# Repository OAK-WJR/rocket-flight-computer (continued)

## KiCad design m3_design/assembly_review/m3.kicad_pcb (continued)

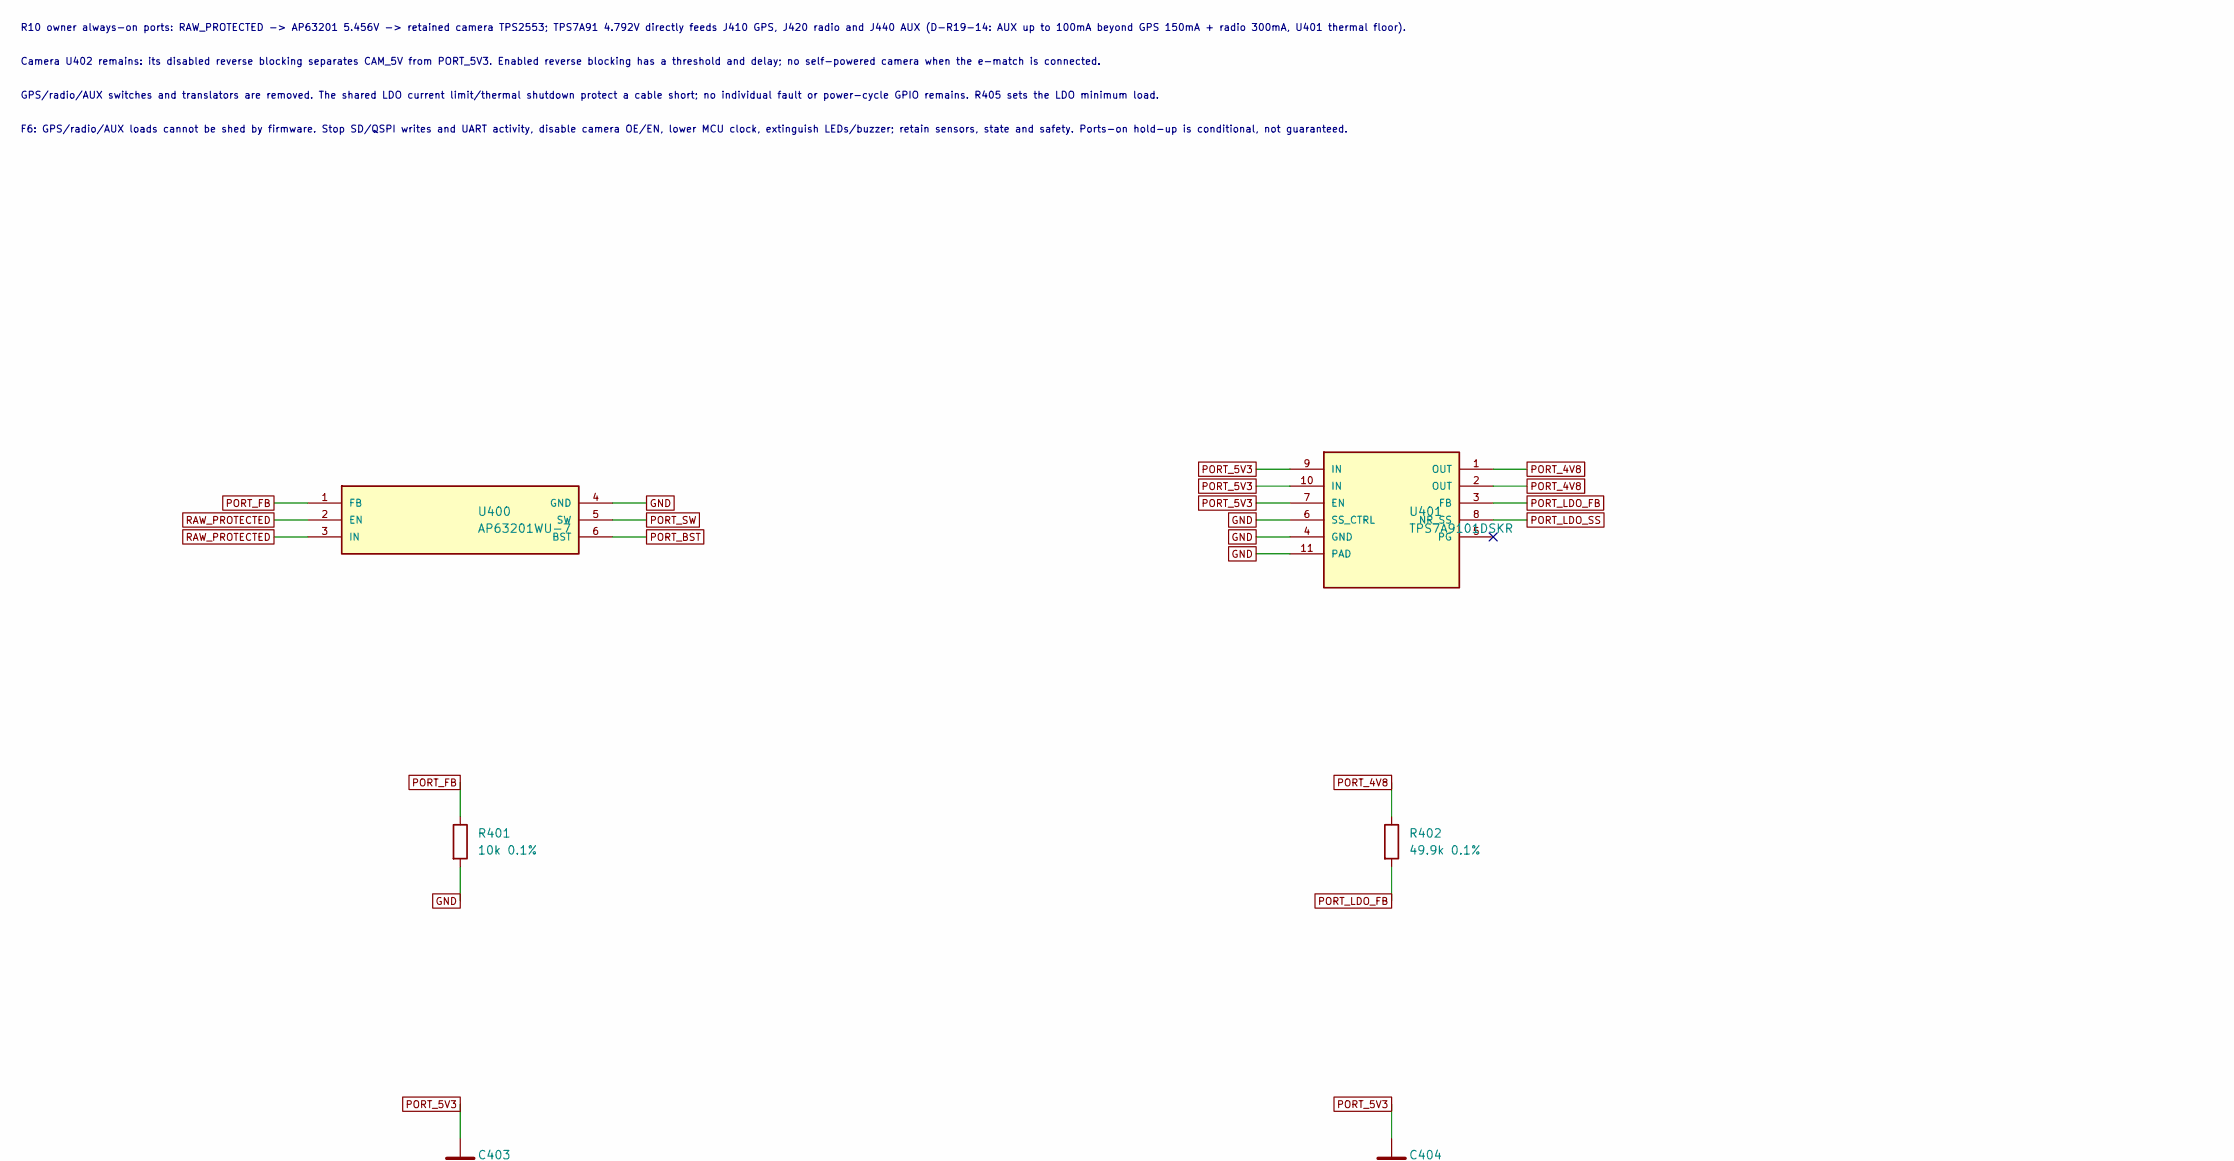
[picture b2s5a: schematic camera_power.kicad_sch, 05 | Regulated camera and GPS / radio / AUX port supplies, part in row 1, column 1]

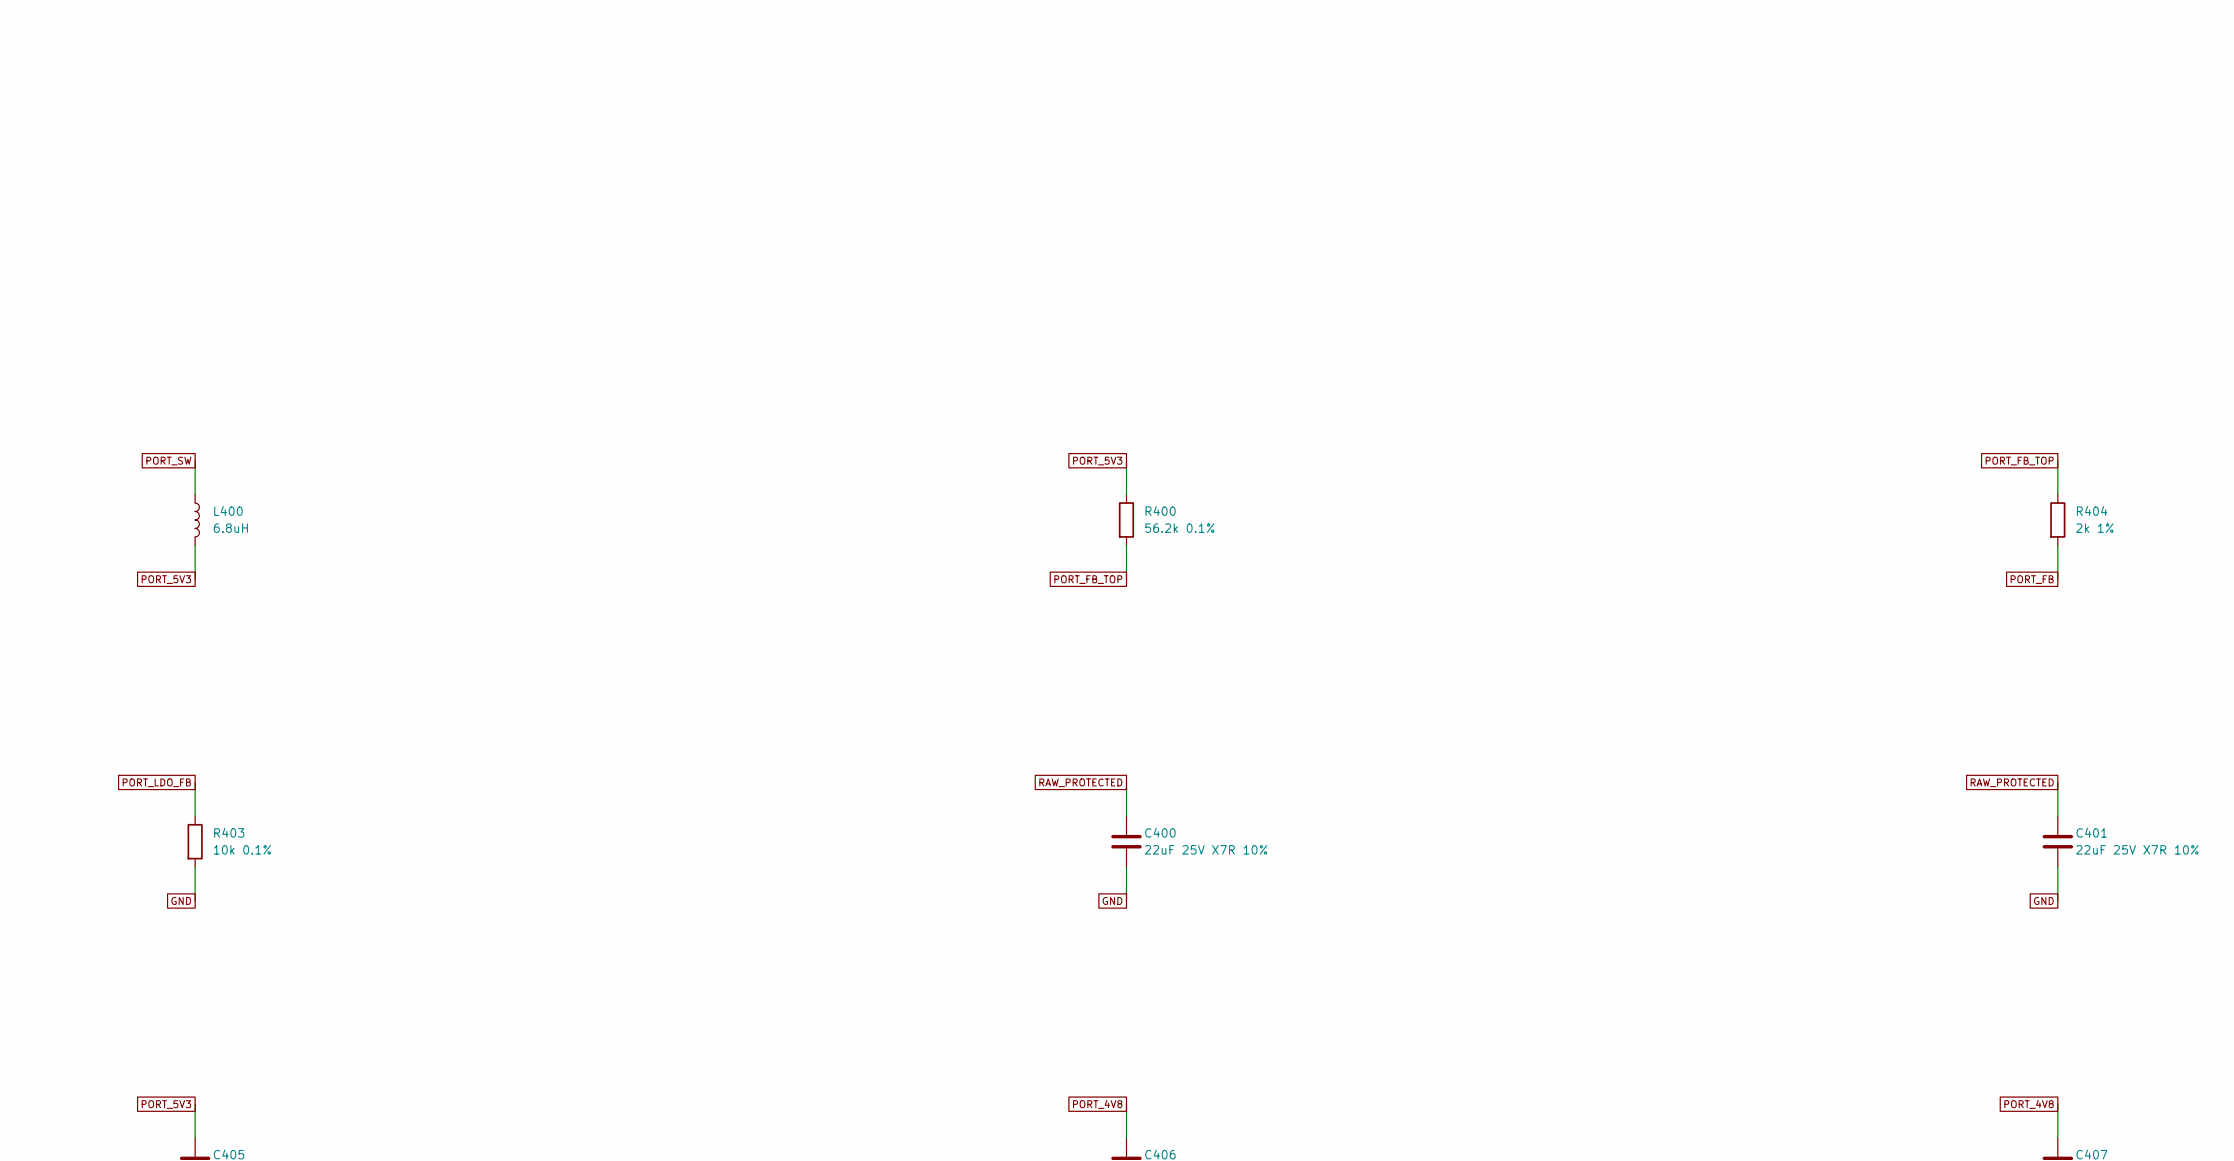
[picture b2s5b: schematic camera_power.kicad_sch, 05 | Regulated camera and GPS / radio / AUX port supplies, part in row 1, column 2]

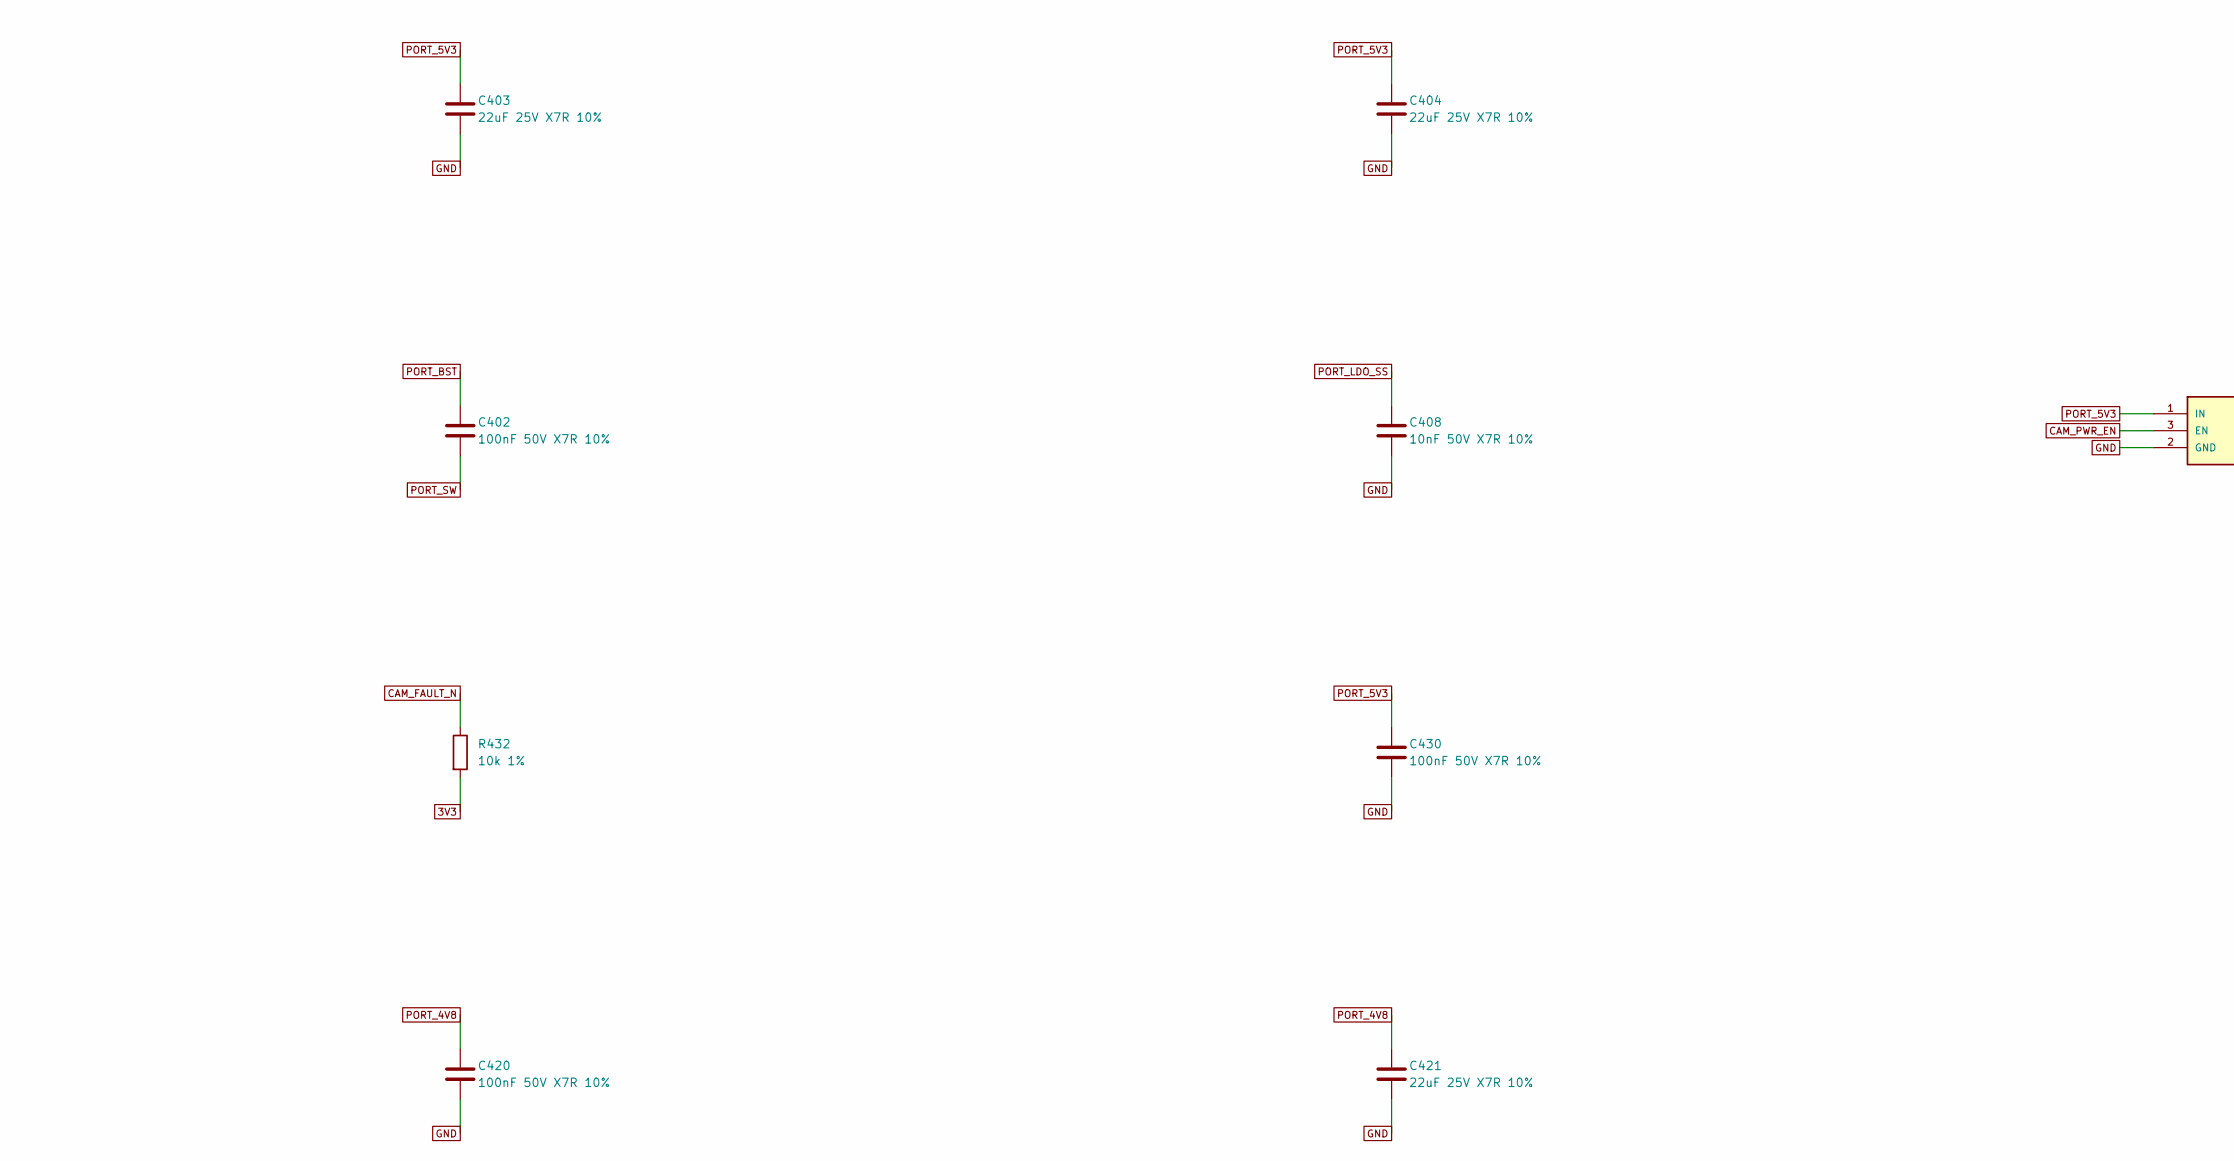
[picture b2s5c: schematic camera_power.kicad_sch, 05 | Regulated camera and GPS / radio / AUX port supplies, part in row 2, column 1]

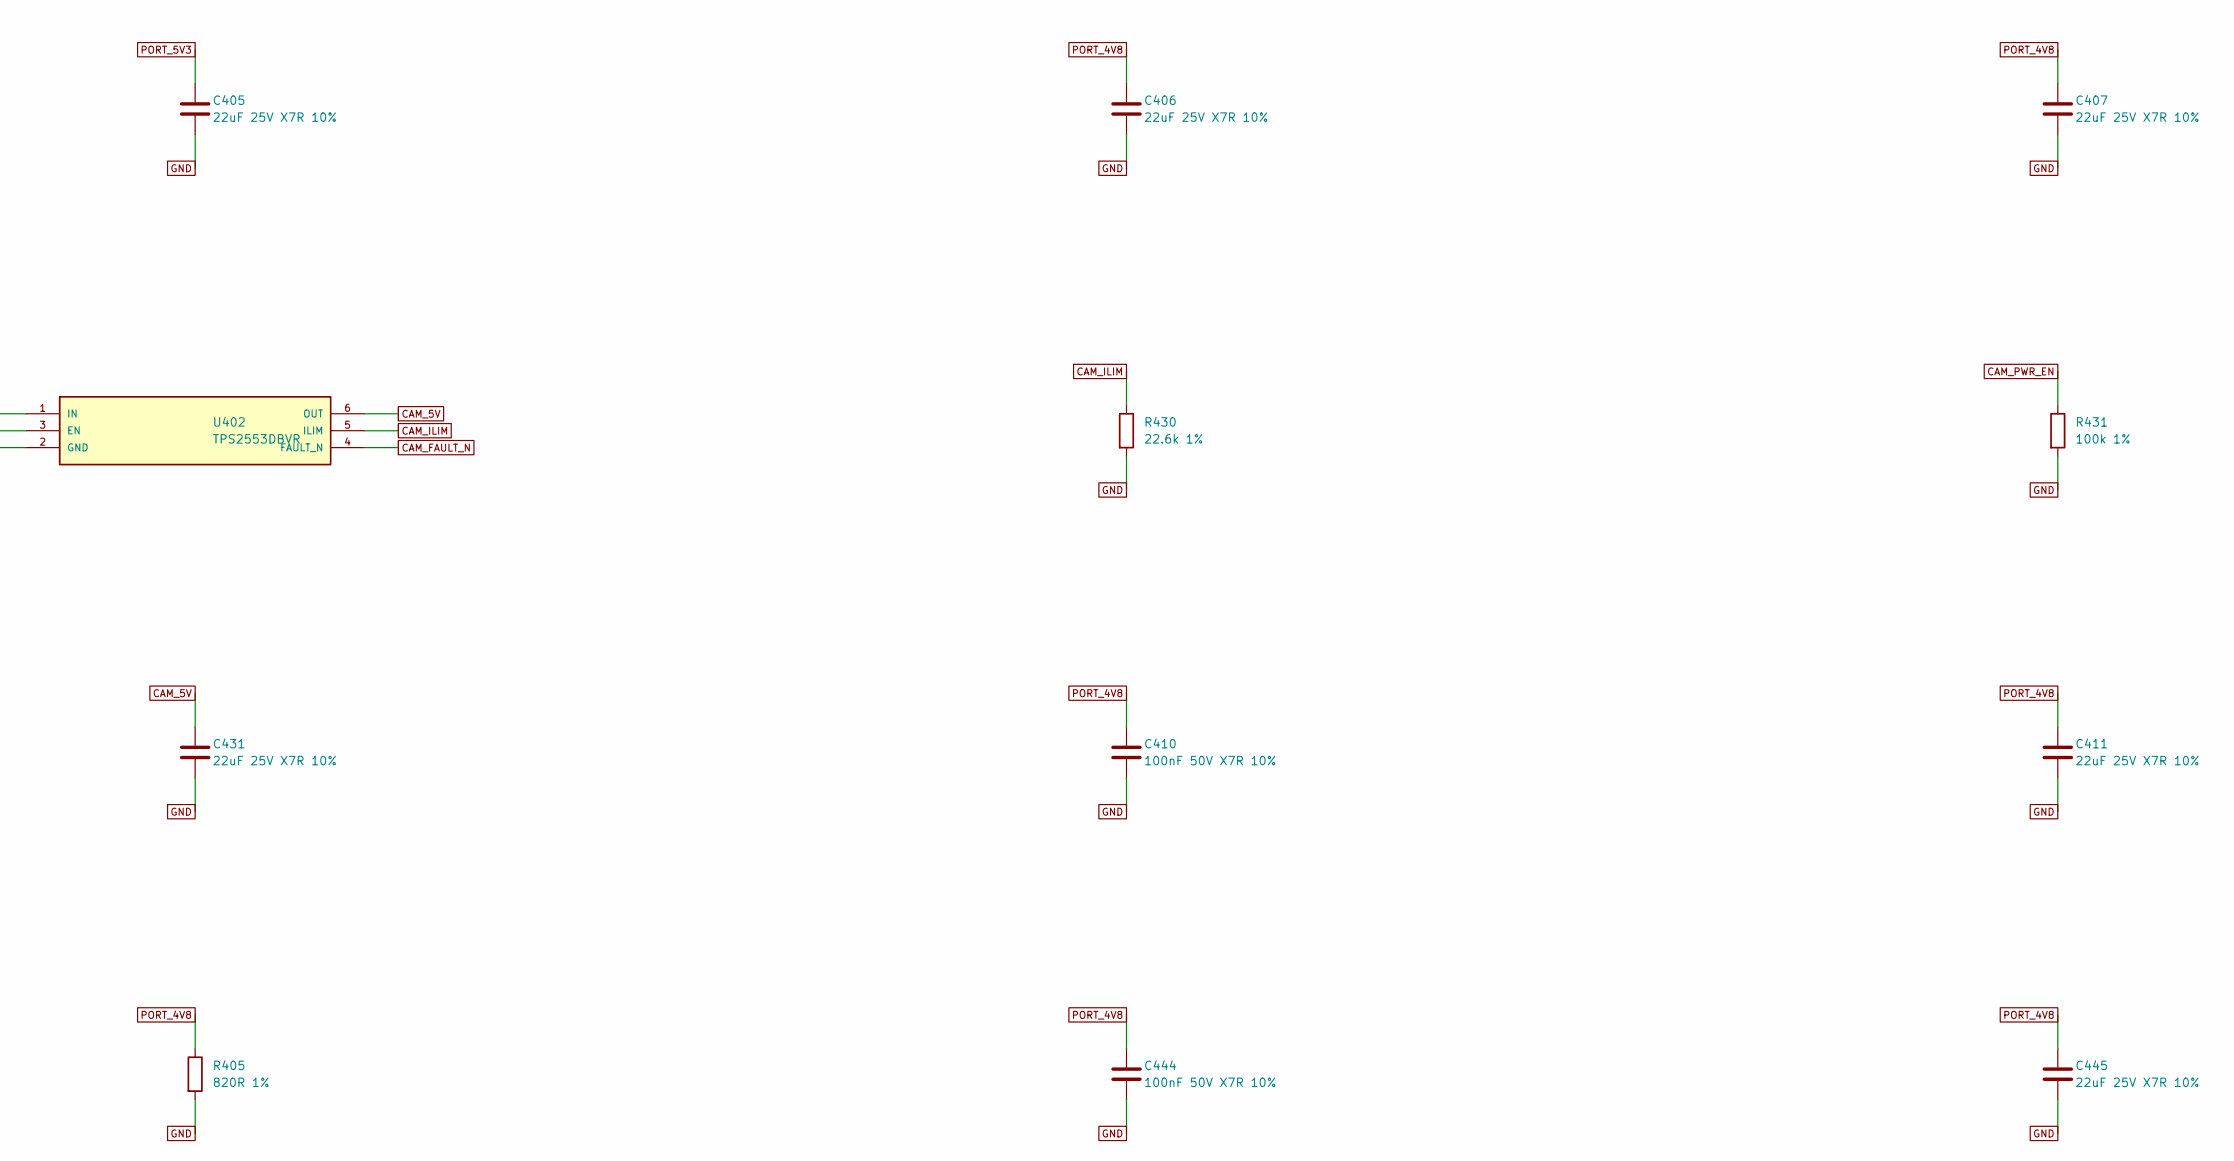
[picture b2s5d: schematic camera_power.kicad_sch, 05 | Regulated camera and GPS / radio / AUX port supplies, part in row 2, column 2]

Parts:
C400, C401, C403, C404, C405, C406, C407, C411, C421, C431, C445: 22uF 25V X7R 10%; M3_GRM32_1210; Manufacturer Part GRM32ER71E226KE15L; LCSC C21397
C402, C410, C420, C430, C444: 100nF 50V X7R 10%; C_0603_1608Metric; Manufacturer Part CC0603KRX7R9BB104; LCSC C14663
C408: 10nF 50V X7R 10%; C0402; Manufacturer Part CL05B103KB5NNNC; LCSC C15195
L400: 6.8uH; M3_SRP5030TA; Manufacturer Part SRP5030T-6R8M; LCSC C1329837
R400: 56.2k 0.1%; R_0603_1608Metric; Manufacturer Part RT0603BRD0756K2L; LCSC C705784
R401, R403: 10k 0.1%; R_0603_1608Metric; Manufacturer Part RT0603BRD0710KL; LCSC C95204
R402: 49.9k 0.1%; R_0603_1608Metric; Manufacturer Part RT0603BRD0749K9L; LCSC C705780
R404: 2k 1%; R_0603_1608Metric; Manufacturer Part 0603WAF2001T5E; LCSC C22975
R405: 820R 1%; R_0603_1608Metric; Manufacturer Part 0603WAF8200T5E; LCSC C23253
R430: 22.6k 1%; R_0603_1608Metric; Manufacturer Part FRC0603F2262TS; LCSC C2999509
R431: 100k 1%; R_0603_1608Metric; Manufacturer Part RC0603FR-07100KL; LCSC C14675
R432: 10k 1%; R0402; Manufacturer Part 0402WGF1002TCE; LCSC C25744
U400: AP63201WU-7; M3_AP63200_TSOT26; Manufacturer Part AP63201WU-7; LCSC C2071044
U401: TPS7A9101DSKR; M3_TPS7A91_DSK10; Manufacturer Part TPS7A9101DSKR; LCSC C2878140
U402: TPS2553DBVR; M3_TPS2553_DBV; Manufacturer Part TPS2553DBVR; LCSC C55266

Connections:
3V3: R432.2; also elsewhere on the board
CAM_5V: C431.1, U402.6 (OUT); also elsewhere on the board
CAM_FAULT_N: R432.1, U402.4 (FAULT_N); also elsewhere on the board
CAM_ILIM: R430.1, U402.5 (ILIM)
CAM_PWR_EN: R431.1, U402.3 (EN); also elsewhere on the board
GND: C400.2, C401.2, C403.2, C404.2, C405.2, C406.2, C407.2, C408.2, C410.2, C411.2, C420.2, C421.2, C430.2, C431.2, C444.2, C445.2, R401.2, R403.2, R405.2, R430.2, R431.2, U400.4 (GND), U401.4 (GND), U401.6 (SS_CTRL), U401.11 (PAD), U402.2 (GND); also elsewhere on the board
PORT_4V8: C406.1, C407.1, C410.1, C411.1, C420.1, C421.1, C444.1, C445.1, R402.1, R405.1, U401.1 (OUT), U401.2 (OUT); also elsewhere on the board
PORT_5V3: C403.1, C404.1, C405.1, C430.1, L400.2, R400.1, U401.7 (EN), U401.9 (IN), U401.10 (IN), U402.1 (IN)
PORT_BST: C402.1, U400.6 (BST)
PORT_FB: R401.1, R404.2, U400.1 (FB)
PORT_FB_TOP: R400.2, R404.1
PORT_LDO_FB: R402.2, R403.1, U401.3 (FB)
PORT_LDO_SS: C408.1, U401.8 (NR_SS)
PORT_SW: C402.2, L400.1, U400.5 (SW)
RAW_PROTECTED: C400.1, C401.1, U400.2 (EN), U400.3 (IN); also elsewhere on the board

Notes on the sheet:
R10 owner always-on ports: RAW_PROTECTED -> AP63201 5.456V -> retained camera TPS2553; TPS7A91 4.792V directly feeds J410 GPS, J420 radio and J440 AUX (D-R19-14: AUX up to 100mA beyond GPS 150mA + radio 300mA, U401 thermal floor).
Camera U402 remains: its disabled reverse blocking separates CAM_5V from PORT_5V3. Enabled reverse blocking has a threshold and delay; no self-powered camera when the e-match is connected.
GPS/radio/AUX switches and translators are removed. The shared LDO current limit/thermal shutdown protect a cable short; no individual fault or power-cycle GPIO remains. R405 sets the LDO minimum load.
F6: GPS/radio/AUX loads cannot be shed by firmware. Stop SD/QSPI writes and UART activity, disable camera OE/EN, lower MCU clock, extinguish LEDs/buzzer; retain sensors, state and safety. Ports-on hold-up is conditional, not guaranteed.

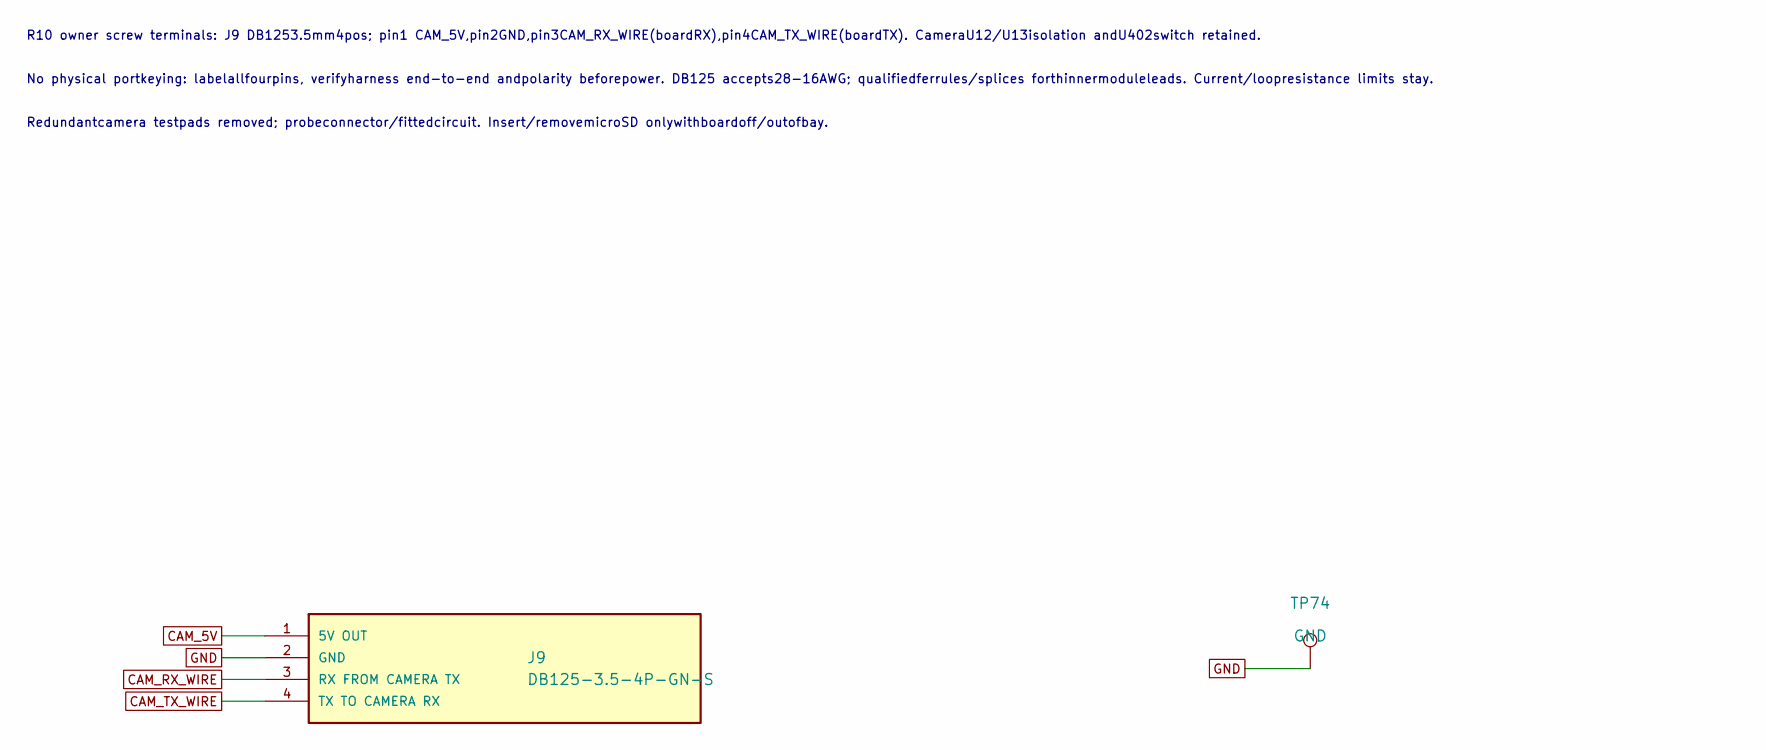
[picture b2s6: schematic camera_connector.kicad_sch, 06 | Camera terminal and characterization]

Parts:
J9: DB125-3.5-4P-GN-S; M3_DB125_4P_GN; Manufacturer Part DB125-3.5-4P-GN-S; LCSC C2757925
TP74: GND; M3_TestPad_1.5

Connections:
CAM_5V: J9.1 (5V OUT); also elsewhere on the board
CAM_RX_WIRE: J9.3 (RX FROM CAMERA TX); also elsewhere on the board
CAM_TX_WIRE: J9.4 (TX TO CAMERA RX); also elsewhere on the board
GND: J9.2 (GND), TP74.1; also elsewhere on the board

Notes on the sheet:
R10 owner screw terminals: J9 DB1253.5mm4pos; pin1 CAM_5V,pin2GND,pin3CAM_RX_WIRE(boardRX),pin4CAM_TX_WIRE(boardTX). CameraU12/U13isolation andU402switch retained.
No physical portkeying: labelallfourpins, verifyharness end-to-end andpolarity beforepower. DB125 accepts28-16AWG; qualifiedferrules/splices forthinnermoduleleads. Current/loopresistance limits stay.
Redundantcamera testpads removed; probeconnector/fittedcircuit. Insert/removemicroSD onlywithboardoff/outofbay.

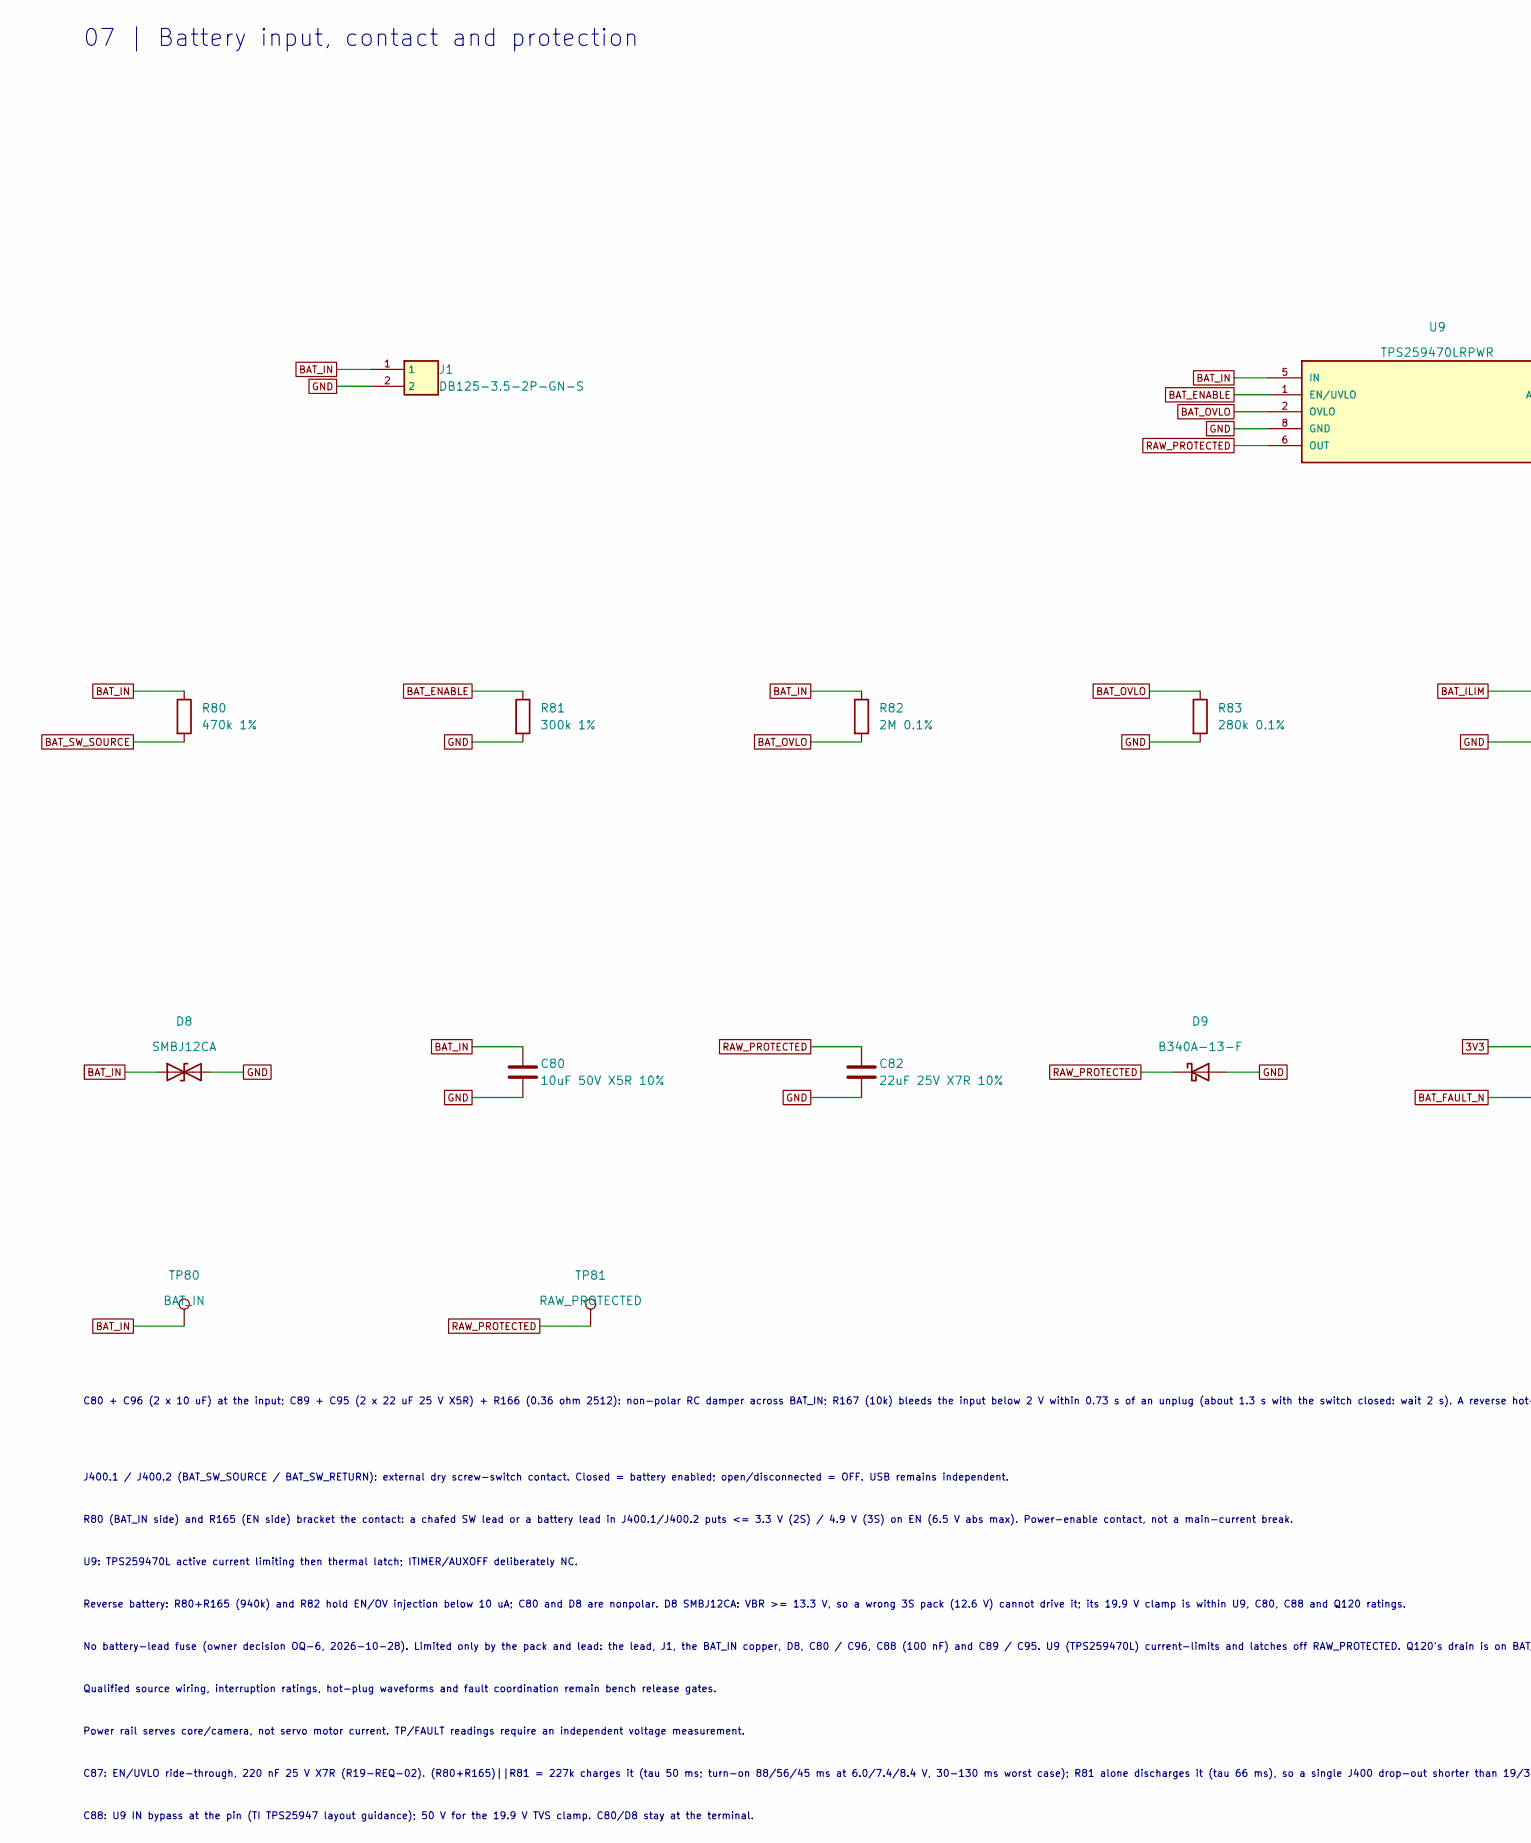
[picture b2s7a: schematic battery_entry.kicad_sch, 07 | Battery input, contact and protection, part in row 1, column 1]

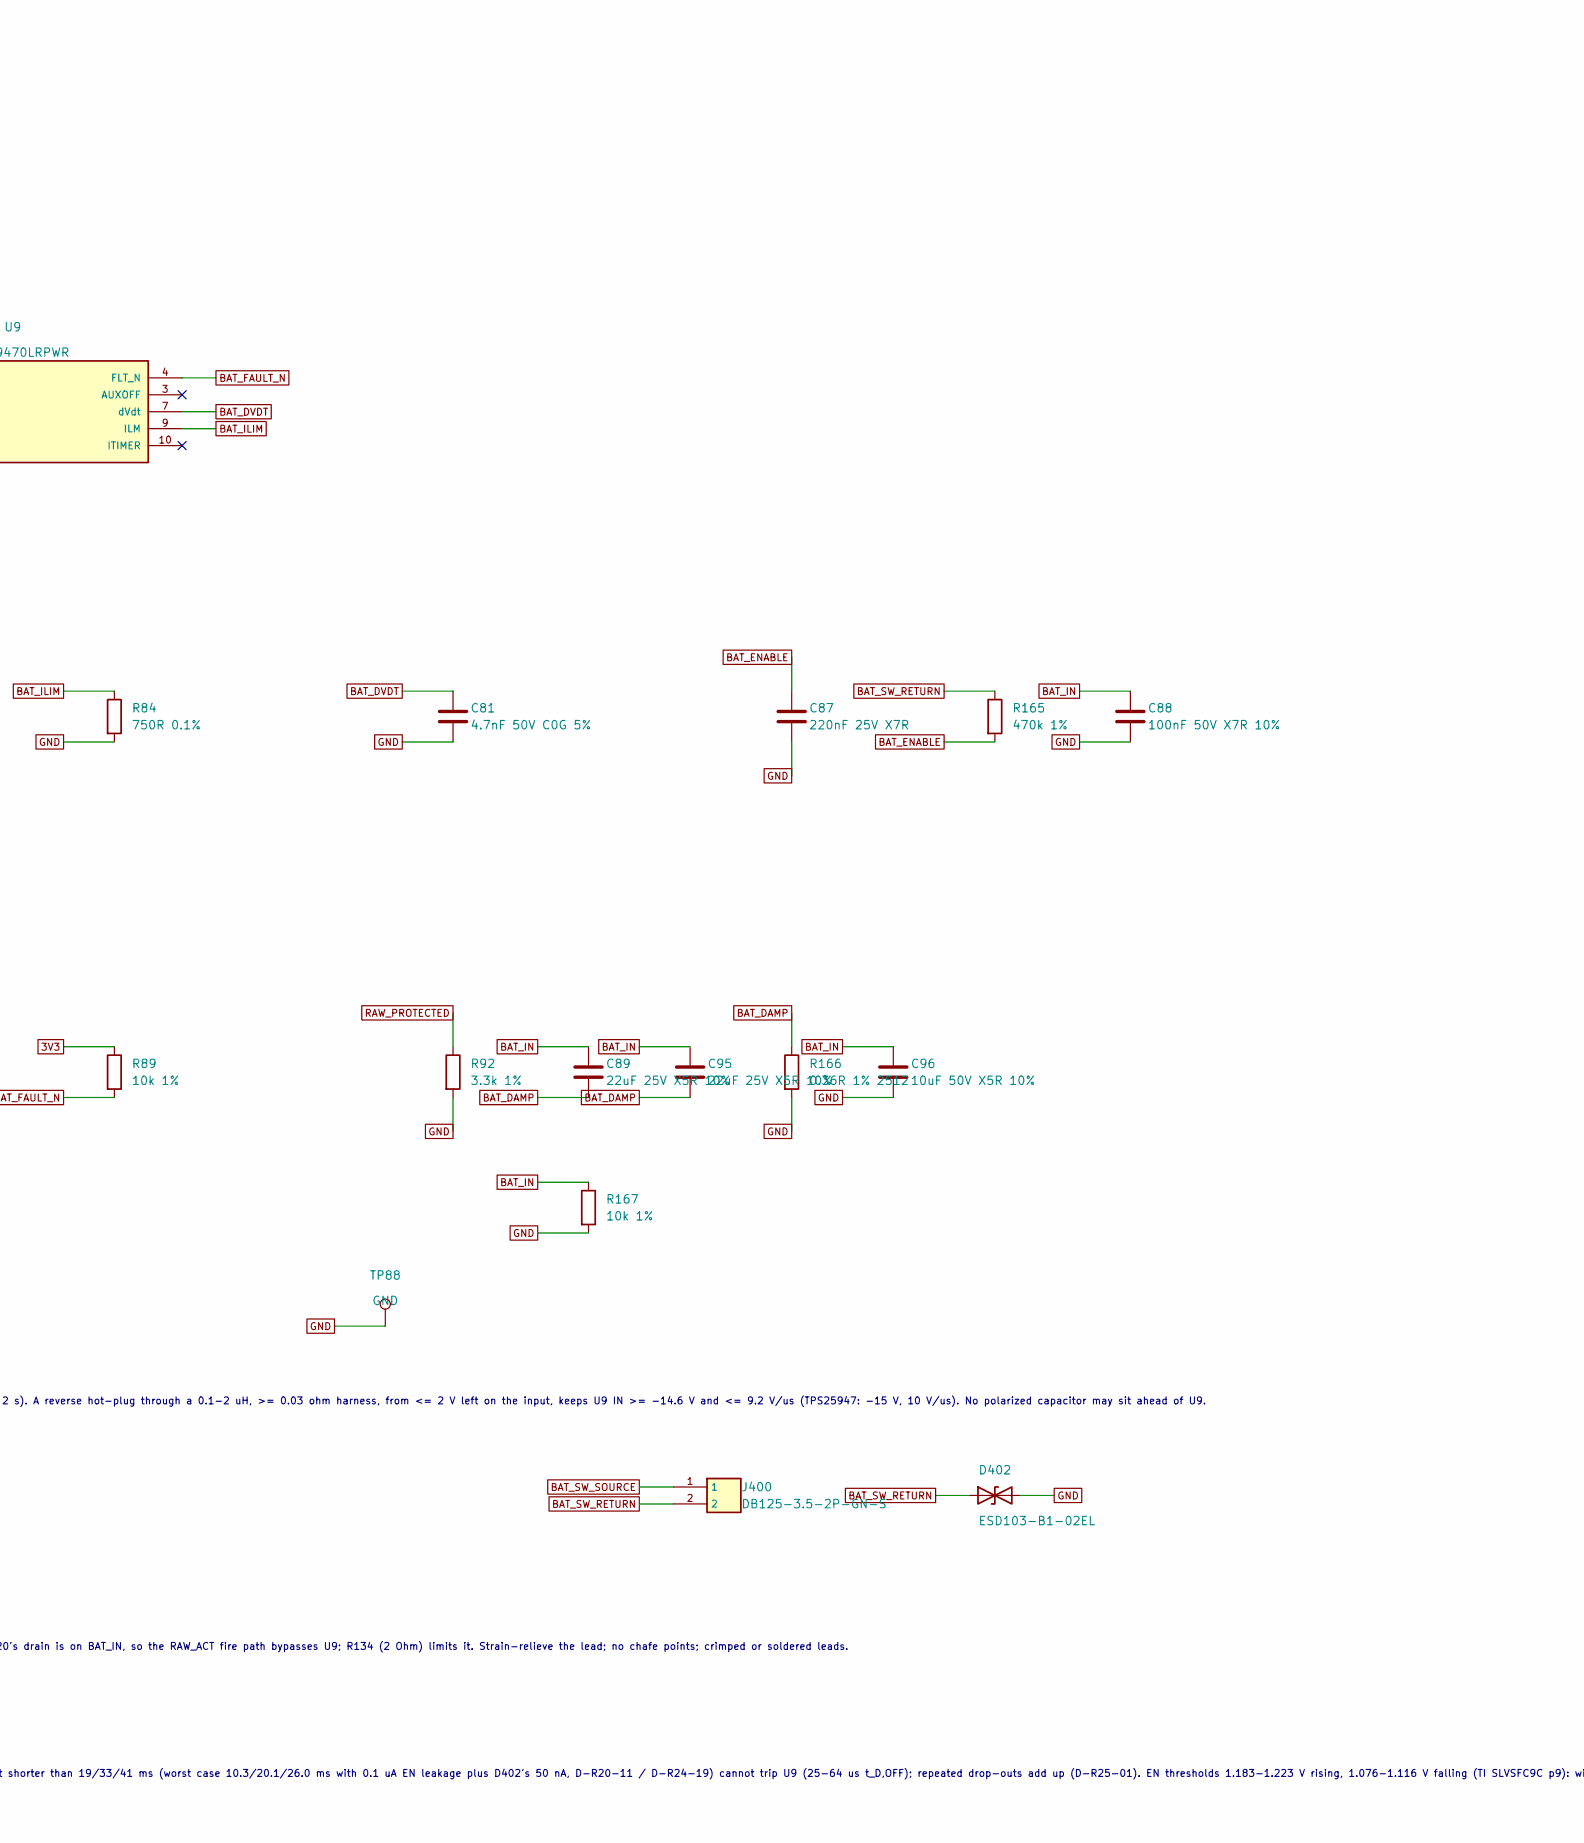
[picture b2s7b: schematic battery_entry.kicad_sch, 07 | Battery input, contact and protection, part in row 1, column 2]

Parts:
C80, C96: 10uF 50V X5R 10%; C_1206_3216Metric; Manufacturer Part CL31A106KBHNNNE; LCSC C13585
C81: 4.7nF 50V C0G 5%; C_0603_1608Metric; Manufacturer Part GRM1885C1H472JA01D; LCSC C85980
C82: 22uF 25V X7R 10%; M3_GRM32_1210; Manufacturer Part GRM32ER71E226KE15L; LCSC C21397
C87: 220nF 25V X7R; C0603; Manufacturer Part CL10B224KA8NNNC; LCSC C21120
C88: 100nF 50V X7R 10%; C0402; Manufacturer Part CL05B104KB54PNC; LCSC C307331
C89, C95: 22uF 25V X5R 10%; C_1206_3216Metric; Manufacturer Part CL31A226KAHNNNE; LCSC C12891
D8: SMBJ12CA; D_SMB; Manufacturer Part SMBJ12CA; LCSC C83849
D9: B340A-13-F; D_SMA; Manufacturer Part B340A-13-F; LCSC C85098
D402: ESD103-B1-02EL; M3_TSLP_2_20; Manufacturer Part ESD103-B1-02EL E6327; LCSC C535146
J1, J400: DB125-3.5-2P-GN-S; M3_DB125_2P_GN; Manufacturer Part DB125-3.5-2P-GN-S; LCSC C466970
R80, R165: 470k 1%; R_0603_1608Metric; Manufacturer Part 0603WAF4703T5E; LCSC C23178
R81: 300k 1%; R_0603_1608Metric; Manufacturer Part 0603WAF3003T5E; LCSC C23024
R82: 2M 0.1%; R_0603_1608Metric; Manufacturer Part MCT0603MD2004BP500; LCSC C4241878
R83: 280k 0.1%; R_0603_1608Metric; Manufacturer Part RT0603BRD07280KL; LCSC C705755
R84: 750R 0.1%; R_0603_1608Metric; Manufacturer Part RT0603BRD07750RL; LCSC C861551
R89, R167: 10k 1%; R_0603_1608Metric; Manufacturer Part 0603WAF1002T5E; LCSC C25804
R92: 3.3k 1%; R_0603_1608Metric; Manufacturer Part 0603WAF3301T5E; LCSC C22978
R166: 0.36R 1% 2512; M3_R2512_UR; Manufacturer Part 25121WF360LT4E; LCSC C168925
TP80: BAT_IN; M3_TestPad_1.5
TP81: RAW_PROTECTED; M3_TestPad_1.5
TP88: GND; M3_TestPad_1.5
U9: TPS259470LRPWR; M3_TPS25947_RPW; Manufacturer Part TPS259470LRPWR; LCSC C3662793

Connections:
3V3: R89.1; also elsewhere on the board
BAT_DAMP: C89.2, C95.2, R166.1
BAT_DVDT: C81.1, U9.7 (dVdt)
BAT_ENABLE: C87.1, R81.1, R165.2, U9.1 (EN/UVLO)
BAT_FAULT_N: R89.2, U9.4 (FLT_N); also elsewhere on the board
BAT_ILIM: R84.1, U9.9 (ILM)
BAT_IN: C80.1, C88.1, C89.1, C95.1, C96.1, D8.1 (A1), J1.1, R80.1, R82.1, R167.1, TP80.1, U9.5 (IN); also elsewhere on the board
BAT_OVLO: R82.2, R83.1, U9.2 (OVLO)
BAT_SW_RETURN: D402.1 (A1), J400.2, R165.1
BAT_SW_SOURCE: J400.1, R80.2
GND: C80.2, C81.2, C82.2, C87.2, C88.2, C96.2, D8.2 (A2), D9.2 (A), D402.2 (A2), J1.2, R81.2, R83.2, R84.2, R92.2, R166.2, R167.2, TP88.1, U9.8 (GND); also elsewhere on the board
RAW_PROTECTED: C82.1, D9.1 (K), R92.1, TP81.1, U9.6 (OUT); also elsewhere on the board

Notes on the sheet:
07 | Battery input, contact and protection
J400.1 / J400.2 (BAT_SW_SOURCE / BAT_SW_RETURN): external dry screw-switch contact. Closed = battery enabled; open/disconnected = OFF. USB remains independent.
R80 (BAT_IN side) and R165 (EN side) bracket the contact: a chafed SW lead or a battery lead in J400.1/J400.2 puts <= 3.3 V (2S) / 4.9 V (3S) on EN (6.5 V abs max). Power-enable contact, not a main-current break.
U9: TPS259470L active current limiting then thermal latch; ITIMER/AUXOFF deliberately NC.
Reverse battery: R80+R165 (940k) and R82 hold EN/OV injection below 10 uA; C80 and D8 are nonpolar. D8 SMBJ12CA: VBR >= 13.3 V, so a wrong 3S pack (12.6 V) cannot drive it; its 19.9 V clamp is within U9, C80, C88 and Q120 ratings.
Qualified source wiring, interruption ratings, hot-plug waveforms and fault coordination remain bench release gates.
Power rail serves core/camera, not servo motor current. TP/FAULT readings require an independent voltage measurement.
C88: U9 IN bypass at the pin (TI TPS25947 layout guidance); 50 V for the 19.9 V TVS clamp. C80/D8 stay at the terminal.
C80 + C96 (2 x 10 uF) at the input; C89 + C95 (2 x 22 uF 25 V X5R) + R166 (0.36 ohm 2512): non-polar RC damper across BAT_IN; R167 (10k) bleeds the input below 2 V within 0.73 s of an unplug (about 1.3 s with the switch closed: wait 2 s). A reverse hot-plug through a 0.1-2 uH, >= 0.03 ohm harness, 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
C87: EN/UVLO ride-through, 220 nF 25 V X7R (R19-REQ-02). (R80+R165)||R81 = 227k charges it (tau 50 ms; turn-on 88/56/45 ms at 6.0/7.4/8.4 V, 30-130 ms worst case); R81 alone discharges it (tau 66 ms), so a single J400 drop-out shorter than 19/33/41 ms (worst case 10.3/20.1/26.0 ms with 0.1 uA EN le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
No battery-lead fuse (owner decision OQ-6, 2026-10-28). Limited only by the pack and lead: the lead, J1, the BAT_IN copper, D8, C80 / C96, C88 (100 nF) and C89 / C95. U9 (TPS259470L) current-limits and latches off RAW_PROTECTED. Q120's drain is on BAT_IN, so the RAW_ACT fire path bypasses U9; R134 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
